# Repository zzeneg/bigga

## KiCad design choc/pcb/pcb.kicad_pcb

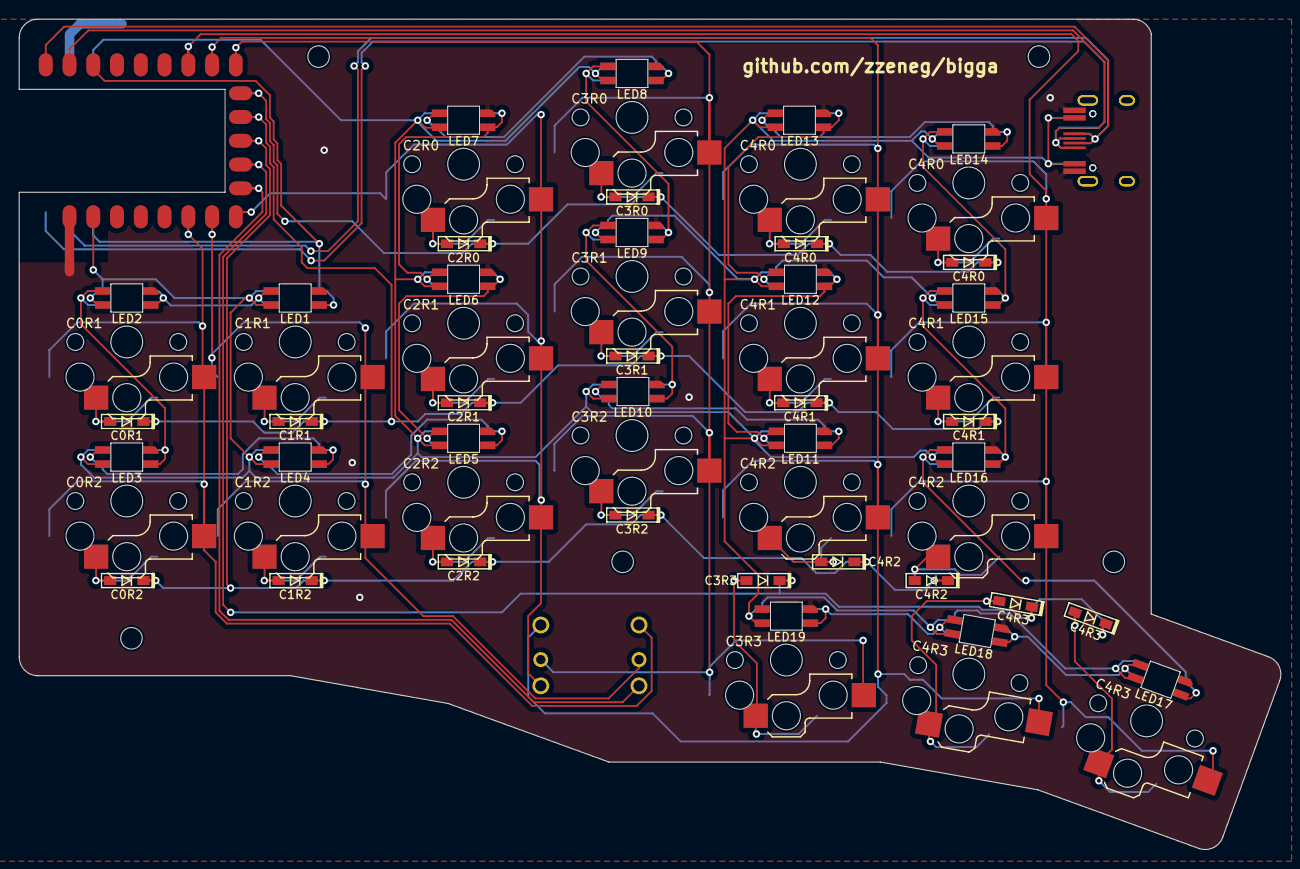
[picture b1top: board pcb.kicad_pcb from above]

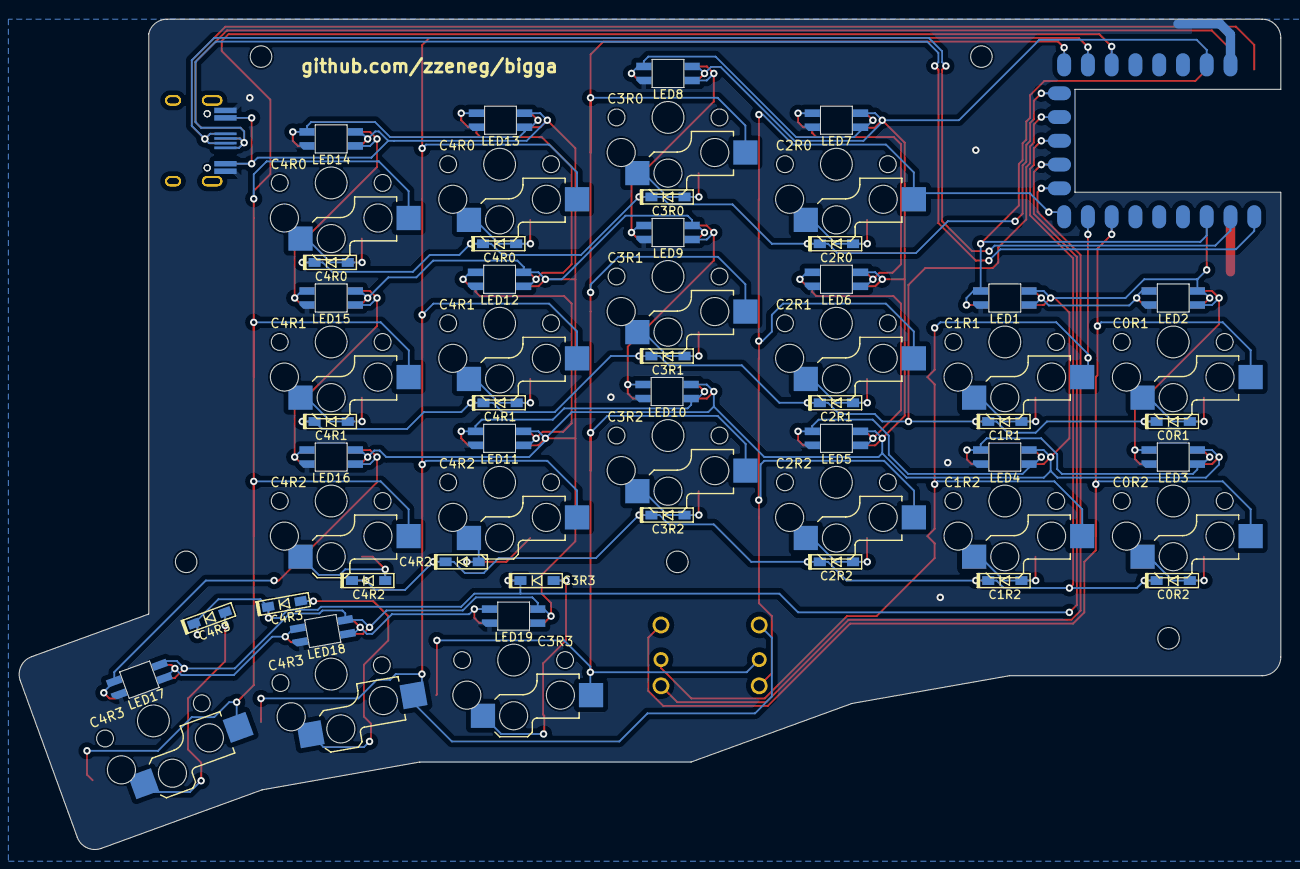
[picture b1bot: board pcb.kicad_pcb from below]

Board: 2 copper layers, 134.8 x 88.7 mm, 67 parts (21 on the bottom side), 53 nets.

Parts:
D1, D2, D3, D4, D5, D6, D7, D8, D9, D10, D11, D12, D13, D14, D15, D16, D17, D18, D19: D; Diode_1N4148-SOD123-reversible-flip3d
FiveWay1: 5Way-Tactile_K1-1506DN-01; Button_5way-reversible
H1, H2, H3, H4, H5: MountingHole; Hole_M2
LED1, LED2, LED3, LED4, LED5, LED6, LED7, LED8, LED9, LED10, LED11, LED12, LED13, LED14, LED15, LED16, LED17, LED18, LED19: YS-SK6812MINI-E; LED_SK6812-MINI-E-reversible-flip3d
MCU1, MCU2: rp2040-zero; MCU_rp2040-zero-smd
SW1, SW2, SW3, SW4, SW5, SW6, SW7, SW8, SW9, SW10, SW11, SW12, SW13, SW14, SW15, SW16, SW17, SW18, SW19: Switch; Switch_ChocV1-hotswap-reversible
USB1, USB2: Connector_HRO-TYPE-C-31-M-12; Connector_HRO-TYPE-C-31-M-12-data

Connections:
GND: LED1.3 (VSS), LED2.3 (VSS), LED3.3 (VSS), LED4.3 (VSS), LED5.3 (VSS), LED6.3 (VSS), LED7.3 (VSS), LED8.3 (VSS), LED9.3 (VSS), LED10.3 (VSS), LED11.3 (VSS), LED12.3 (VSS), LED13.3 (VSS), LED14.3 (VSS), LED15.3 (VSS), LED16.3 (VSS), LED17.3 (VSS), LED18.3 (VSS), LED19.3 (VSS), MCU1.22 (GND), MCU2.22 (GND), USB1.1 (GND), USB1.12 (GND), USB2.1 (GND), USB2.12 (GND)
LED: LED1.4 (DIN), MCU1.3 (2), MCU2.3 (2)
unnamed: D1.2 (A), SW1.1
unnamed: D2.2 (A), SW2.1
unnamed: D3.2 (A), SW3.1
unnamed: D4.2 (A), SW4.1
unnamed: D5.2 (A), SW5.1
unnamed: D6.2 (A), SW6.1
unnamed: D7.2 (A), SW7.1
unnamed: D8.2 (A), SW8.1
unnamed: D9.2 (A), SW9.1
unnamed: D10.2 (A), SW10.1
unnamed: D11.2 (A), SW11.1
unnamed: D12.2 (A), SW12.1
unnamed: D13.2 (A), SW13.1
unnamed: D14.2 (A), SW14.1
unnamed: D15.2 (A), SW15.1
unnamed: D16.2 (A), SW16.1
unnamed: D17.2 (A), SW17.1
unnamed: D18.2 (A), SW18.1
unnamed: D19.2 (A), SW19.1
unnamed: LED1.2 (DOUT), LED2.4 (DIN)
unnamed: LED2.2 (DOUT), LED3.4 (DIN)
unnamed: LED3.2 (DOUT), LED4.4 (DIN)
unnamed: LED4.2 (DOUT), LED5.4 (DIN)
unnamed: LED5.2 (DOUT), LED6.4 (DIN)
unnamed: LED6.2 (DOUT), LED7.4 (DIN)
unnamed: LED7.2 (DOUT), LED8.4 (DIN)
unnamed: LED8.2 (DOUT), LED9.4 (DIN)
unnamed: LED9.2 (DOUT), LED10.4 (DIN)
unnamed: LED10.2 (DOUT), LED11.4 (DIN)
unnamed: LED11.2 (DOUT), LED12.4 (DIN)
unnamed: LED12.2 (DOUT), LED13.4 (DIN)
unnamed: LED13.2 (DOUT), LED14.4 (DIN)
unnamed: LED14.2 (DOUT), LED15.4 (DIN)
unnamed: LED15.2 (DOUT), LED16.4 (DIN)
unnamed: LED16.2 (DOUT), LED17.4 (DIN)
unnamed: LED17.2 (DOUT), LED18.4 (DIN)
unnamed: LED18.2 (DOUT), LED19.4 (DIN)
RX: MCU1.2 (1), MCU2.1 (0), USB1.5 (DN2), USB1.7 (DN1), USB2.6 (DP1), USB2.8 (DP2)
TX: MCU1.1 (0), MCU2.2 (1), USB1.6 (DP1), USB1.8 (DP2), USB2.5 (DN2), USB2.7 (DN1)
VCC: LED1.1 (VDD), LED2.1 (VDD), LED3.1 (VDD), LED4.1 (VDD), LED5.1 (VDD), LED6.1 (VDD), LED7.1 (VDD), LED8.1 (VDD), LED9.1 (VDD), LED10.1 (VDD), LED11.1 (VDD), LED12.1 (VDD), LED13.1 (VDD), LED14.1 (VDD), LED15.1 (VDD), LED16.1 (VDD), LED17.1 (VDD), LED18.1 (VDD), LED19.1 (VDD), MCU1.21 (3V3), MCU2.21 (3V3), USB1.2 (VBUS), USB1.11 (VBUS), USB2.2 (VBUS), USB2.11 (VBUS)
col0: FiveWay1.6, MCU1.17 (26), MCU2.7 (6), SW5.2, SW11.2
col1: FiveWay1.5, MCU1.16 (15), MCU2.8 (7), SW6.2, SW12.2
col2: FiveWay1.3, MCU1.15 (14), MCU2.9 (8), SW1.2, SW7.2, SW13.2
col3: FiveWay1.2, MCU1.9 (8), MCU2.15 (14), SW2.2, SW8.2, SW14.2, SW17.2
col4: FiveWay1.1, MCU1.8 (7), MCU2.16 (15), SW3.2, SW9.2, SW15.2, SW18.2
col5: MCU1.7 (6), MCU2.17 (26), SW4.2, SW10.2, SW16.2, SW19.2
row0: D1.1 (K), D2.1 (K), D3.1 (K), D4.1 (K), MCU1.10 (9), MCU2.14 (13)
row1: D5.1 (K), D6.1 (K), D7.1 (K), D8.1 (K), D9.1 (K), D10.1 (K), MCU1.11 (10), MCU2.13 (12)
row2: D11.1 (K), D12.1 (K), D13.1 (K), D14.1 (K), D15.1 (K), D16.1 (K), MCU1.12 (11), MCU2.12 (11)
row3: D17.1 (K), D18.1 (K), D19.1 (K), MCU1.13 (12), MCU2.11 (10)
row4: FiveWay1.4, MCU1.14 (13), MCU2.10 (9)

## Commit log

2023-08-26 first draft
2023-08-26 second
2023-08-26 third
2023-08-27 forth
2023-08-27 small updates
2023-08-27 fifth
2023-08-27 sixth
2023-08-28 v1.0
2023-09-06 restructure project
